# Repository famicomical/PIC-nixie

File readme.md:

# PIC-nixie #
Design of a simple yet accurate Nixie clock controlled by a single-chip MCU. 

Logic Board:

Socket Board for IN-14 Tubes:

The socket PCB plugs into the logic board to make an 'L' shape.

The time is displayed on four tubes with MUX-ed cathodes. The digits are output in binary-coded decimal for interfacing with the K155ID1 cathode driver. Anodes and the colon bulb (12:34) are also controlled by the PIC through BJT-pMOS level shifters.

The program tracks time such that the bottle-neck for clock accuracy will be the external oscillator. Anode blanking was implemented to ensure fast transitions on the Nixie tubes without ghosting (with help from a Zener diode). The clock will also run an outgassing routine every hour to prevent "cathode poisoning" and even out wear to lengthen tube life.

A CR2032 battery can be installed on the circuit board to provide backup power in the event of an outage. The tubes may go dark but the MCU will continue to run and keep time for about 11 hours until power is restored.

## Design

The PCB assembly is housed in a 'C'-shaped enclosure, which obscures the tops of the neon tubes. The design was developed in collaboration with my friend [Donald Swen](https://www.dswenn.com/projects/2019/11/27/22-Design.html) at Stanford's Design School. The idea is that, by hiding the pointed tops of the IN-14 tubes, the finished clock can achieve a symettry that would normally only be possible with IN-12 bulbs. With this clock shape, the vertical digits appear to be floating seamlessly within a cylinder. PIC-Nixie is the first neon tube clock to incorporate this aesthetic design principle.

The enclosure for the prototype was made from stacked slabs of Fraké wood. The clock was a gift for my grandpa.

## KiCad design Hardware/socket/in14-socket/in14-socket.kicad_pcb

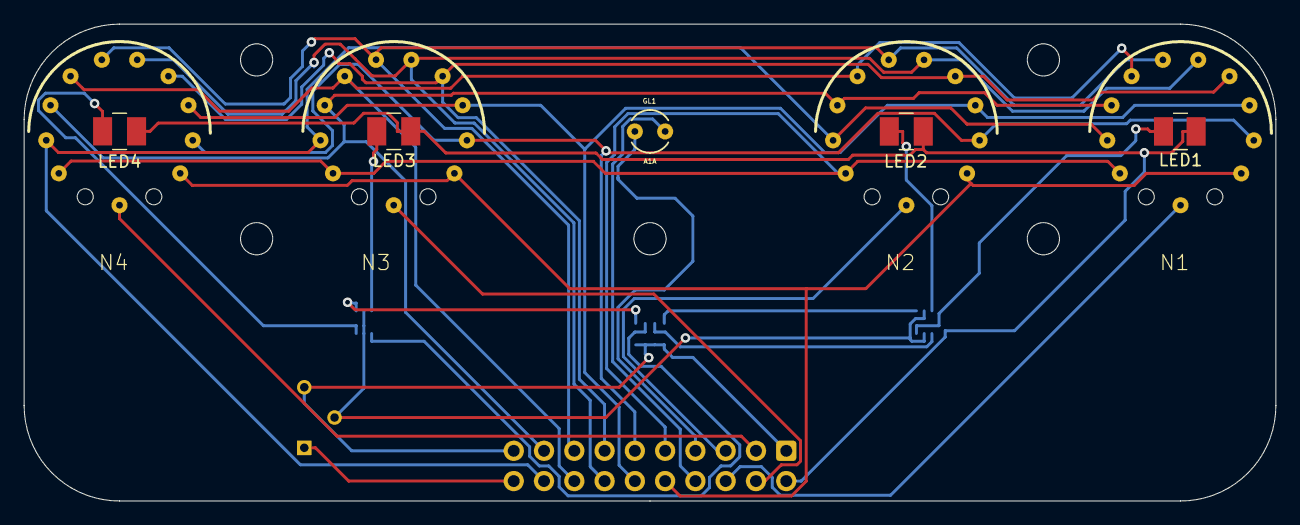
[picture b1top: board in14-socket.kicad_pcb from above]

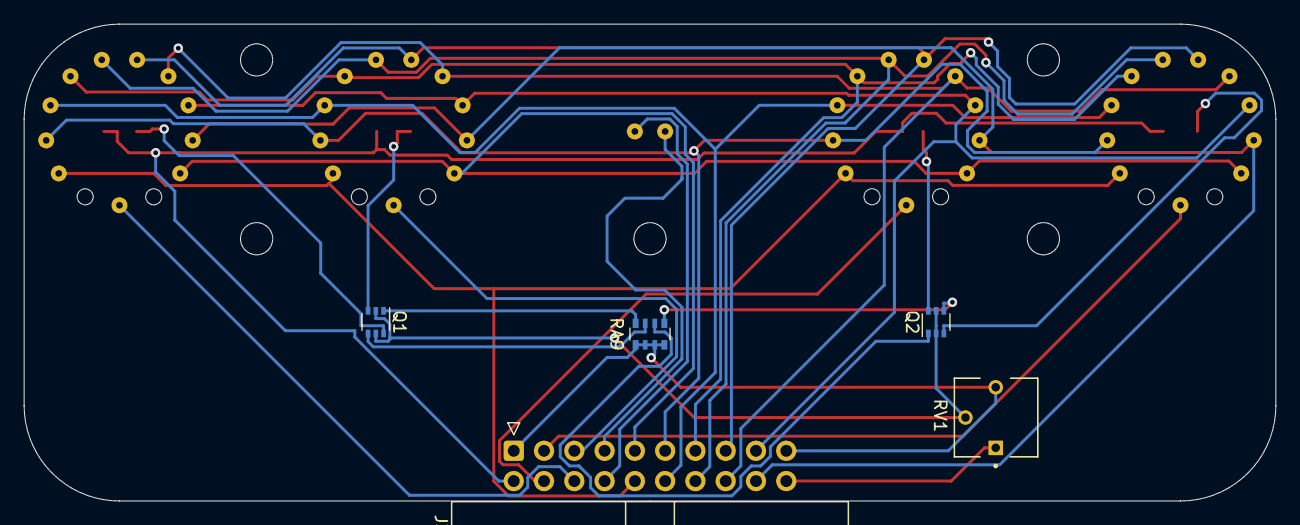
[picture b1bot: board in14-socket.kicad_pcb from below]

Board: 2 copper layers, 105.0 x 40.0 mm, 19 parts (5 on the bottom side), 28 nets.

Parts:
GL1: A1A; NE2-A1A
H1, H2, H3, H4, H5: MountingHole_2.7mm_M2.5
J3: Conn_01x20_Male; IDC-Header_2x10_P2.54mm_Horizontal
LED1, LED2, LED3, LED4: VLMU3100-GS08
N1, N2, N3, N4: Val**; IN-14
Q1, Q2: BC847BS; SOT-363_SC-70-6
RA9: 220 x 4; R_Array_Convex_4x0603
RV1: R_POT_TRIM_US; TRIM_3362P-1-302LF

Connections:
+3V0: J3.20, RV1.1
/HR1: J3.5, N2.A
/HR10: J3.6, N1.A
/MIN1: J3.3, N4.A
/MIN10: J3.4, N3.A
/colon1: GL1.1, J3.7
/colon2: GL1.2, J3.8
GND: J3.1, J3.19, RA9.1, RA9.2, RA9.3, RA9.4, RV1.3
unnamed: J3.9, N1.0, N2.0, N3.0, N4.0
unnamed: J3.10, N1.1, N2.1, N3.1, N4.1
unnamed: J3.11, N1.2, N2.2, N3.2, N4.2
unnamed: J3.12, N1.3, N2.3, N3.3, N4.3
unnamed: J3.13, N1.4, N2.4, N3.4, N4.4
unnamed: J3.14, N1.5, N2.5, N3.5, N4.5
unnamed: J3.15, N1.6, N2.6, N3.6, N4.6
unnamed: J3.16, N1.7, N2.7, N3.7, N4.7
unnamed: J3.17, N1.8, N2.8, N3.8, N4.8
unnamed: J3.18, N1.9, N2.9, N3.9, N4.9
unnamed: LED1.1, Q1.6
unnamed: LED2.1, Q1.3
unnamed: LED3.1, Q2.6
unnamed: LED4.1, Q2.3
unnamed: Q1.1, RA9.8
unnamed: Q1.2, Q1.5, Q2.2, Q2.5, RV1.2
unnamed: Q1.4, RA9.7
unnamed: Q2.1, RA9.6
unnamed: Q2.4, RA9.5
VCC: J3.2, LED1.2, LED2.2, LED3.2, LED4.2

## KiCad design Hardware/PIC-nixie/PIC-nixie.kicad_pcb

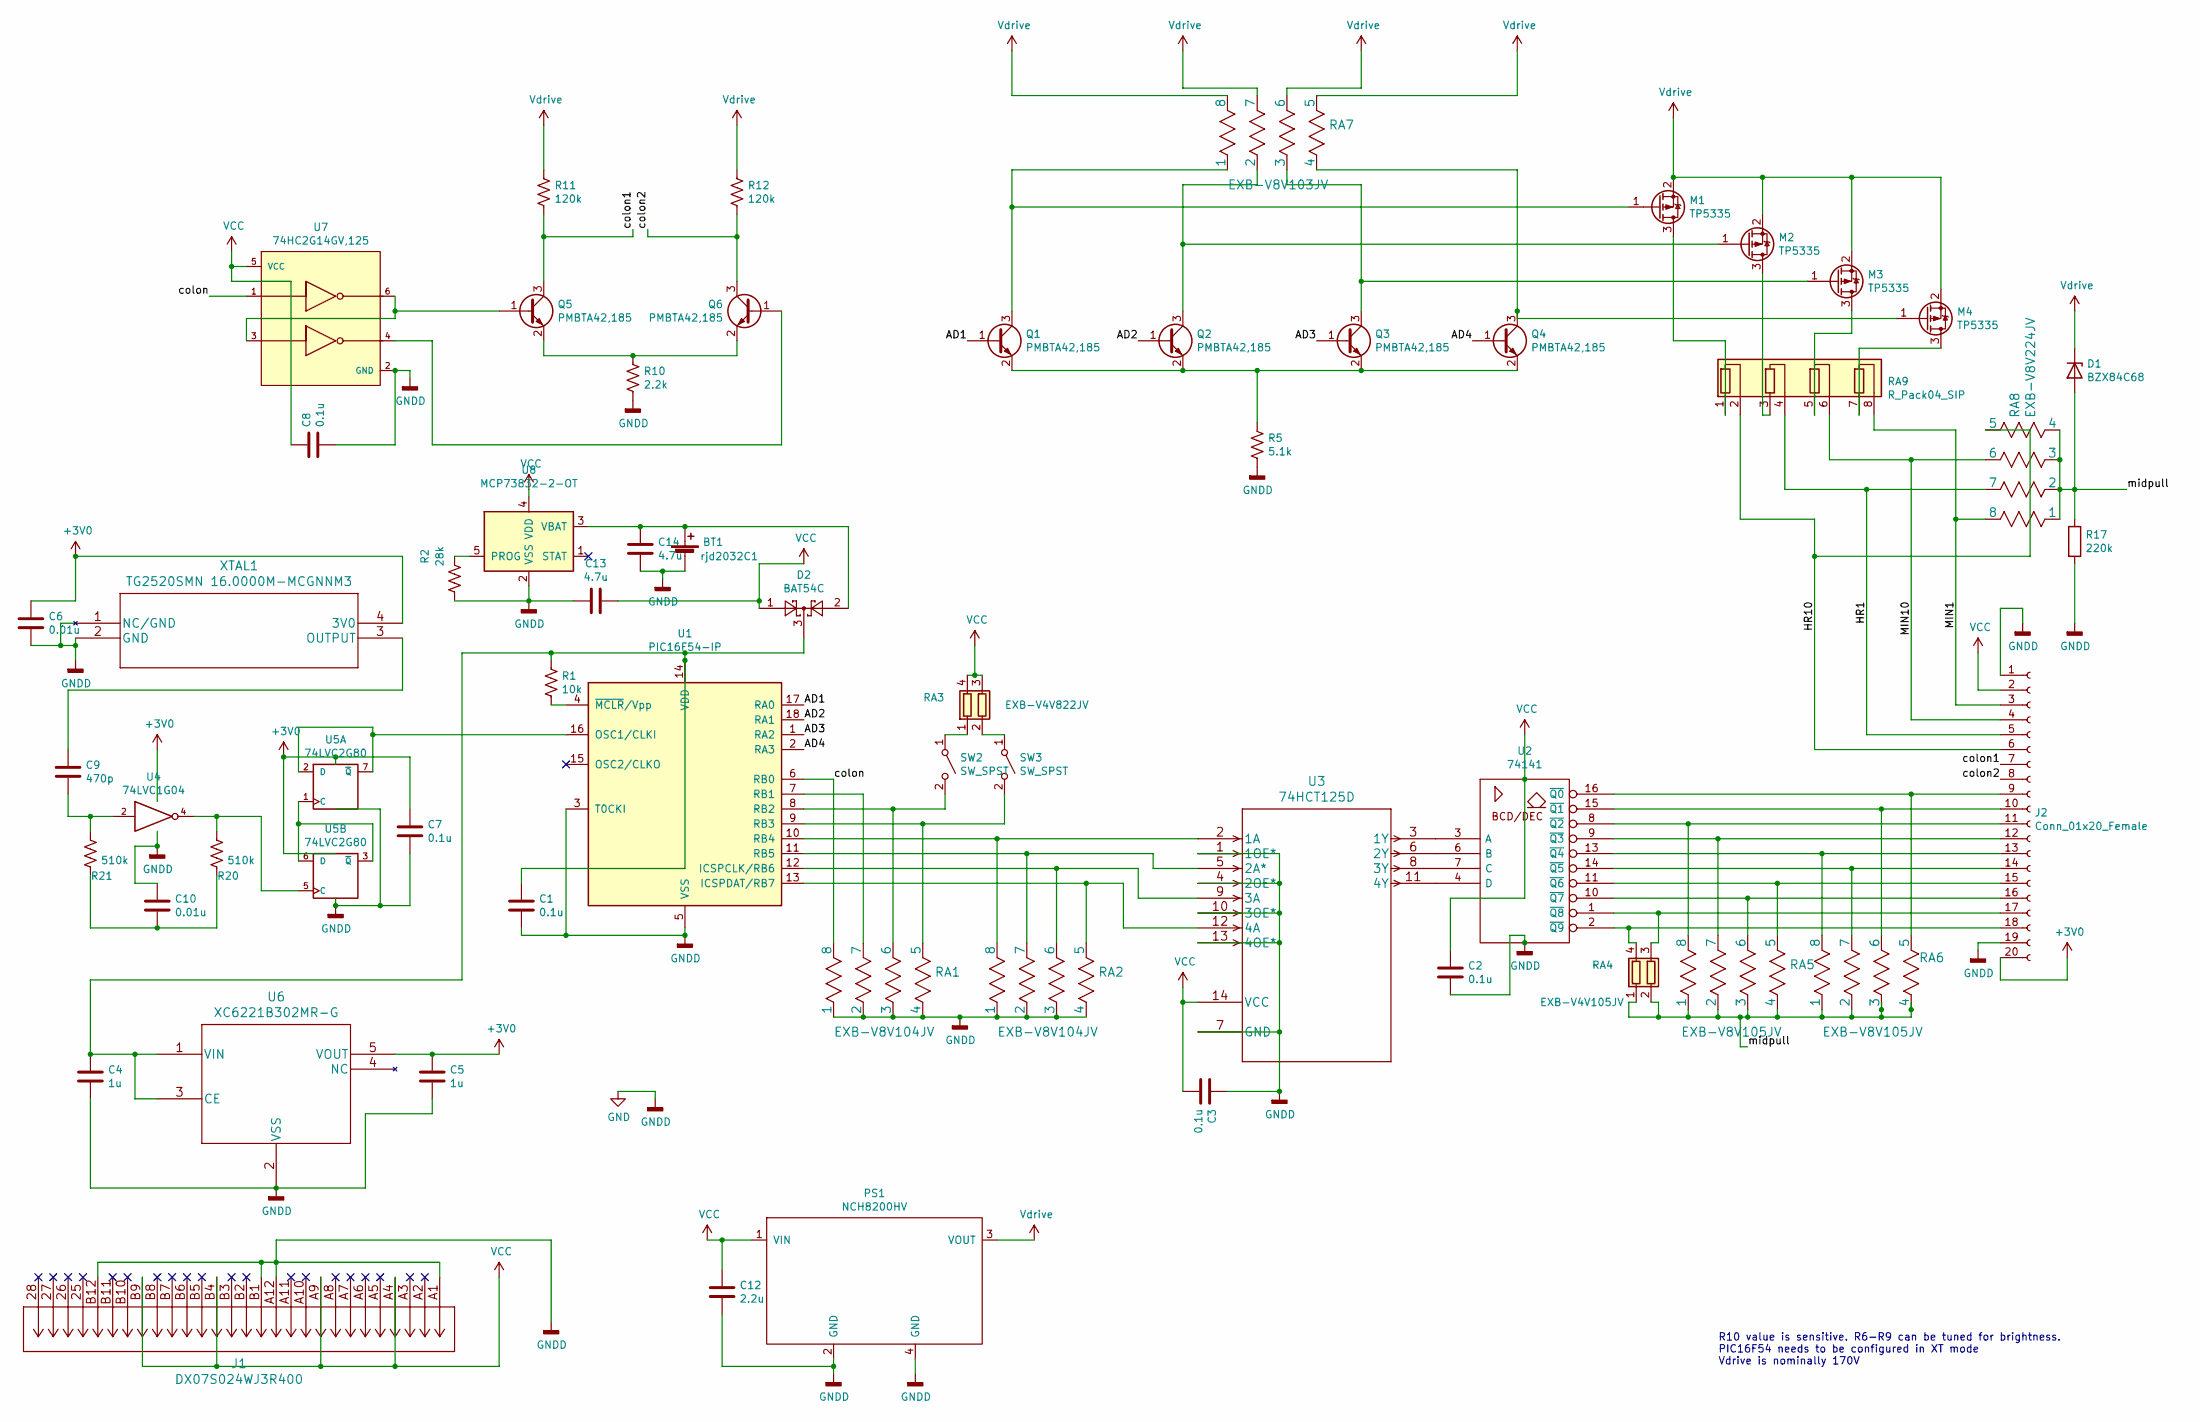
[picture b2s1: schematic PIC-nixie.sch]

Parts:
BT1: rjd2032C1; BatteryHolder_Keystone_1060_1x2032
C1, C2, C3, C7, C8: 0.1u; C_0603_1608Metric_Pad1.05x0.95mm_HandSolder
C4, C5: 1u; C_0603_1608Metric_Pad1.05x0.95mm_HandSolder
C6, C10: 0.01u; C_0603_1608Metric_Pad1.05x0.95mm_HandSolder
C9: 470p; C_0603_1608Metric_Pad1.05x0.95mm_HandSolder
C12: 2.2u; C_0805_2012Metric_Pad1.15x1.40mm_HandSolder
C13, C14: 4.7u; C_0805_2012Metric_Pad1.15x1.40mm_HandSolder
D1: BZX84C68; D_SOT-23_ANK
D2: BAT54C; SOT-23
J1: DX07S024WJ3R400; JAE_DX07S024WJ3R400
J2: Conn_01x20_Female; IDC-Header_2x10_P2.54mm_Vertical
M1, M2, M3, M4: TP5335; SOT-23
PS1: NCH8200HV
Q1, Q2, Q3, Q4, Q5, Q6: PMBTA42,185; SOT-23
R1: 10k; R_0805_2012Metric_Pad1.15x1.40mm_HandSolder
R2: 28k; R_0805_2012Metric_Pad1.15x1.40mm_HandSolder
R5: 5.1k; R_0805_2012Metric_Pad1.15x1.40mm_HandSolder
R10: 2.2k; R_0805_2012Metric_Pad1.15x1.40mm_HandSolder
R11, R12: 120k; R_0805_2012Metric_Pad1.15x1.40mm_HandSolder
R17: 220k; R_0805_2012Metric_Pad1.15x1.40mm_HandSolder
R20, R21: 510k; R_0603_1608Metric_Pad0.98x0.95mm_HandSolder
RA1, RA2: EXB-V8V104JV; R_Array_Convex_4x0603
RA3: EXB-V4V822JV; R_Array_Convex_2x0603
RA4: EXB-V4V105JV; R_Array_Convex_2x0603
RA5, RA6: EXB-V8V105JV; R_Array_Convex_4x0603
RA7: EXB-V8V103JV; R_Array_Convex_4x0603
RA8: EXB-V8V224JV; R_Array_Convex_4x0603
RA9: R_Pack04_SIP; R_Array_SIP8
SW2, SW3: SW_SPST; SW_TL3301SPF260QG
U1: PIC16F54-IP; DIP-18_W7.62mm_Socket
U2: 74141; DIP-16_W7.62mm_Socket
U3: 74HCT125D; SOIC-14_3.9x8.7mm_P1.27mm
U4: 74LVC1G04; SOT-553
U5: 74LVC2G80; VSSOP-8_2.3x2mm_P0.5mm
U6: XC6221B302MR-G
U7: 74HC2G14GV,125; Nexperia-SOT457-11_2018-0-MFG; mouser part number 771-HC2G14GV125; digikey description IC INVERTER SCHMITT 2CH 6TSOP
U8: MCP73832-2-OT; SOT-23-5
XTAL1: TG2520SMN 16.0000M-MCGNNM3

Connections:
+3V0: C5.1, C6.1, C7.1, J2.20, U4.5 (+V), U5.8 (+V), U6.5 (VOUT), XTAL1.4 (3V0); also elsewhere on the board
/AD1: Q1.1 (B), U1.17 (RA0)
/AD2: Q2.1 (B), U1.18 (RA1)
/AD3: Q3.1 (B), U1.1 (RA2)
/AD4: Q4.1 (B), U1.2 (RA3)
/HR1: J2.5, RA8.7, RA9.4 (R2.2)
/HR10: J2.6, RA8.5, RA9.2 (R1.2)
/MIN1: J2.3, RA8.8, RA9.8 (R4.2)
/MIN10: J2.4, RA8.6, RA9.6 (R3.2)
/colon: RA1.8, U1.6 (RB0), U7.1 (1A)
/colon1: J2.7, Q5.3 (C), R11.2
/colon2: J2.8, Q6.3 (C), R12.2
/midpull: D1.2 (A), R17.1, RA4.1 (R1.1), RA4.2 (R2.1), RA5.1, RA5.2, RA5.3, RA5.4, RA6.1, RA6.2, RA6.3, RA6.4, RA8.1, RA8.2, RA8.3, RA8.4
GND: BT1.2 (-), C1.2, C2.2, C3.1, C4.2, C5.2, C6.2, C7.2, C8.2, C10.1, C12.2, C13.2, C14.2, J1.A1, J1.A12, J1.B1, J1.B12, J2.1, J2.19, PS1.2 (GND), PS1.4 (GND), R2.2, R5.2, R10.2, R17.2, RA1.1, RA1.2, RA1.3, RA1.4, RA2.1, RA2.2, RA2.3, RA2.4, U1.3 (T0CKI), U1.5 (VSS), U2.12 (GND), U3.1 (1OE*), U3.4 (2OE*), U3.7 (GND), U3.10 (3OE*), U3.13 (4OE*), U4.3 (GND), U5.4 (GND), U6.2 (VSS), U7.2 (GND), U8.2 (VSS), XTAL1.1 (NC/GND), XTAL1.2 (GND); also elsewhere on the board
unnamed: BT1.1 (+), C14.1, D2.2, U8.3 (VBAT)
unnamed: C1.1, C4.1, D2.3, R1.1, U1.14 (VDD), U6.1 (VIN), U6.3 (CE)
unnamed 16: C9.1, XTAL1.3 (OUTPUT); also elsewhere on the board
unnamed: C9.2, R21.1, U4.2
unnamed: C10.2, R20.2, R21.2
unnamed: J2.9, RA6.5, U2.16 (~Q0)
unnamed: J2.10, RA6.6, U2.15 (~Q1)
unnamed: J2.11, RA5.8, U2.8 (~Q2)
unnamed: J2.12, RA5.7, U2.9 (~Q3)
unnamed: J2.13, RA6.8, U2.13 (~Q4)
unnamed: J2.14, RA6.7, U2.14 (~Q5)
unnamed: J2.15, RA5.5, U2.11 (~Q6)
unnamed: J2.16, RA5.6, U2.10 (~Q7)
unnamed: J2.17, RA4.3 (R2.2), U2.1 (~Q8)
unnamed: J2.18, RA4.4 (R1.2), U2.2 (~Q9)
unnamed: M1.1 (G), Q1.3 (C), RA7.1
unnamed: M1.3 (D), RA9.1 (R1.1)
unnamed: M2.1 (G), Q2.3 (C), RA7.2
unnamed: M2.3 (D), RA9.3 (R2.1)
unnamed: M3.1 (G), Q3.3 (C), RA7.3
unnamed: M3.3 (D), RA9.5 (R3.1)
unnamed: M4.1 (G), Q4.3 (C), RA7.4
unnamed: M4.3 (D), RA9.7 (R4.1)
unnamed: Q1.2 (E), Q2.2 (E), Q3.2 (E), Q4.2 (E), R5.1
unnamed: Q5.1 (B), U7.3 (2A), U7.6 (1Y)
unnamed: Q5.2 (E), Q6.2 (E), R10.1
unnamed: Q6.1 (B), U7.4 (2Y)
unnamed: R1.2, U1.4 (~MCLR~/Vpp)
unnamed: R2.1, U8.5 (PROG)
unnamed: R20.1, U4.4, U5.5 (C)
unnamed: RA1.5, SW3.2 (B), U1.9 (RB3)
unnamed: RA1.6, SW2.2 (B), U1.8 (RB2)
unnamed: RA1.7, U1.7 (RB1)
unnamed: RA2.5, U1.13 (ICSPDAT/RB7), U3.12 (4A)
unnamed: RA2.6, U1.12 (ICSPCLK/RB6), U3.9 (3A)
unnamed: RA2.7, U1.11 (RB5), U3.5 (2A*)
unnamed: RA2.8, U1.10 (RB4), U3.2 (1A)
unnamed: RA3.1 (R1.1), SW2.1 (A)
unnamed: RA3.2 (R2.1), SW3.1 (A)
unnamed: U1.16 (OSC1/CLKI), U5.2 (D), U5.7 (~Q)
unnamed: U2.3 (A), U3.3 (1Y)
unnamed: U2.4 (D), U3.11 (4Y)
unnamed: U2.6 (B), U3.6 (2Y)
unnamed: U2.7 (C), U3.8 (3Y)
unnamed: U5.1 (C), U5.3 (~Q), U5.6 (D)
VCC: C2.1, C3.2, C8.1, C12.1, C13.1, D2.1, J1.A4, J1.A9, J1.B4, J1.B9, J2.2, PS1.1 (VIN), RA3.3 (R2.2), RA3.4 (R1.2), U2.5 (VCC), U3.14 (VCC), U7.5 (VCC), U8.4 (VDD)
Vdrive: D1.1 (K), M1.2 (S), M2.2 (S), M3.2 (S), M4.2 (S), PS1.3 (VOUT), R11.1, R12.1, RA7.5, RA7.6, RA7.7, RA7.8

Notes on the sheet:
R10 value is sensitive. R6-R9 can be tuned for brightness. PIC16F54 needs to be configured in XT mode Vdrive is nominally 170V

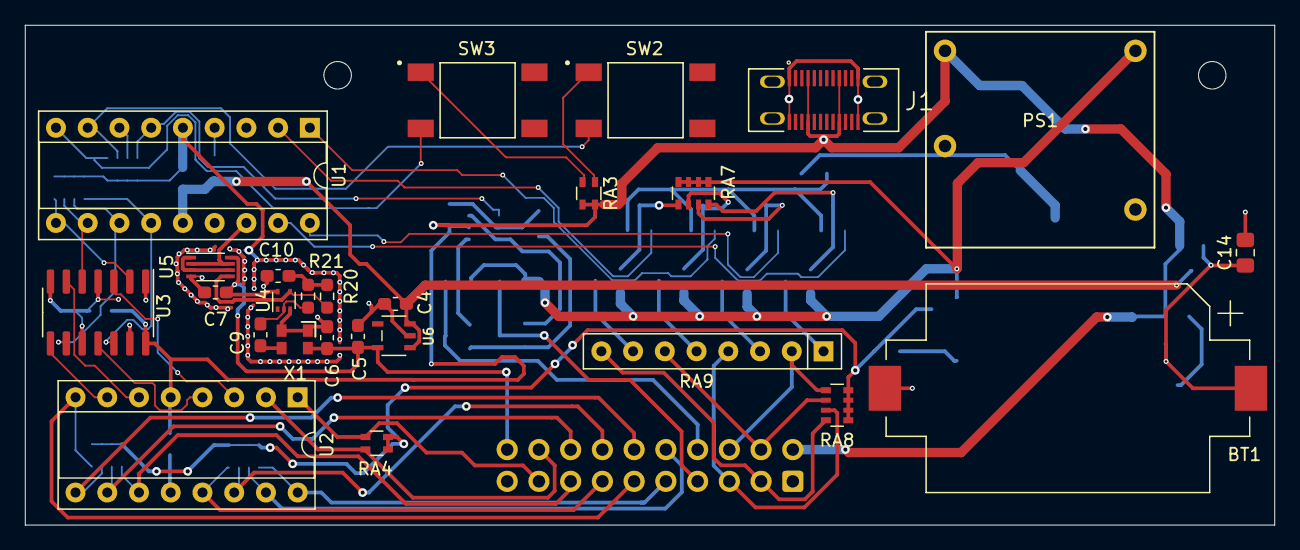
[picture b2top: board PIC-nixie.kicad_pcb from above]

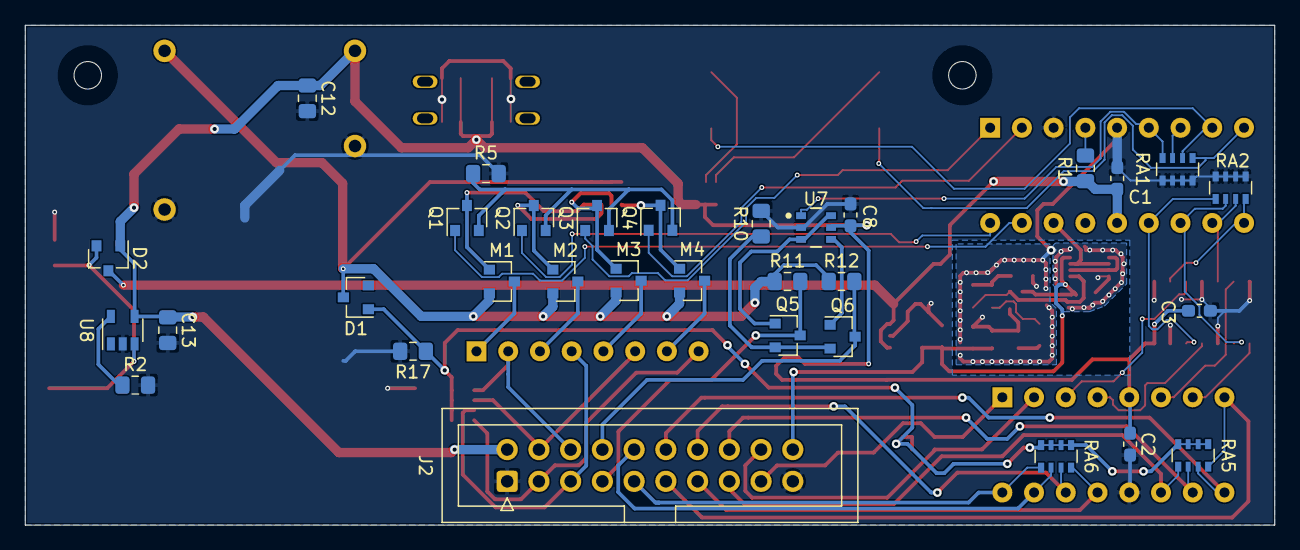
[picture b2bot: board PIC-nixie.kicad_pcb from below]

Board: 2 copper layers, 100.0 x 40.0 mm, 58 parts (32 on the bottom side), 61 nets.

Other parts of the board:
X1: TG2520SMN 16.0000M-MCGNNM3

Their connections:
+3V0: X1.4; also elsewhere on the board
GND: X1.1, X1.2; also elsewhere on the board
unnamed 16: X1.3; also elsewhere on the board

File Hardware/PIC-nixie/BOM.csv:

Item,Reference(s),Value,Footprint,digikey part number,Qty,
1,"C1, C2, C3, C7, C8",0.1u,SM0603,1276-1941-2-ND,5,
2,"C4, C5",1u,SM0603,445-12539-2-ND ,2,
3,"C6, C10",0.01u NP0,SM0603,478-3700-2-ND,2,
4,C9,470p NP0,SM0603,478-5777-2-ND ,1,
5,C11,2.2u film,external:QXK2E225KTP,493-3523-ND,1,
6,C12,2.2u,SM0805,1276-2953-2-ND,1,
7,D1,BZX84C68,SOT-23,BZX84C68LT1GOSTR-ND,1,
8,J1,DX07S024WJ3R400,external:DX07S024WJ3R400,670-2950-2-ND ,1,
9,J2,Conn_01x20_Female,Connector_IDC:IDC-Header_2x10_P2.54mm_Vertical,S9197-ND ,1,
10,"M1, M2, M3, M4",TP5335,SOT-23,TP5335K1-GTR-ND,4,
11,PS1,NCH8200HV,PIC-nixie:NCH8200HV,N/A,1,
12,"Q1, Q2, Q3, Q4, Q5, Q6","PMBTA42,185",SOT-23,1727-8537-2-ND,6,
13,R1,10k,Resistor_SMD:R_0805_2012Metric_Pad1.15x1.40mm_HandSolder,2019-SG73S2ATTD103JTR-ND,1,
14,R5,5.1k,Resistor_SMD:R_0805_2012Metric_Pad1.15x1.40mm_HandSolder,P21099TR-ND,1,
15,R10,2.2k,Resistor_SMD:R_0805_2012Metric_Pad1.15x1.40mm_HandSolder,2019-SG73S2ATTD2201FTR-ND,1,
16,"R11, R12",120k,Resistor_SMD:R_0805_2012Metric_Pad1.15x1.40mm_HandSolder,2019-RK73H2ARTTD1203FTR-ND,2,
17,R17,220k,Resistor_SMD:R_0805_2012Metric_Pad1.15x1.40mm_HandSolder,A126350TR-ND ,1,
18,"R20, R21",510k,Resistor_SMD:R_0603_1608Metric_Pad0.98x0.95mm_HandSolder,YAG4802TR-ND,2,
19,"RA1, RA2, RA7",EXB-V8V103JV,Resistor_SMD:R_Array_Convex_4x0603,Y4103TR-ND,3,
20,RA3,EXB-V8V821JV,Resistor_SMD:R_Array_Convex_4x0603,Y4821TR-ND ,1,
21,RA4,EXB-V4V105JV,Resistor_SMD:R_Array_Convex_2x0603,Y2105TR-ND,1,
22,"RA5, RA6",EXB-V8V105JV,Resistor_SMD:R_Array_Convex_4x0603,Y4105TR-ND,2,
23,RA8,EXB-V8V224JV,Resistor_SMD:R_Array_Convex_4x0603,Y4224TR-ND,1,
24,RA9,4608X-102-822LF,Resistor_THT:R_Array_SIP8,4608X-2-822LF-ND ,1,
25,"SW1, SW2, SW3",SW_SPST,external:SW_TL3301SPF260QG,EG1870TR-ND,3,
26,U1,PIC16F54-IP,Package_DIP:DIP-18_W7.62mm_Socket,"PIC16F54-I/P-ND, ED3318-ND",1,
27,U2,K155ID1,Package_DIP:DIP-16_W7.62mm_Socket,"N/A, ED90033-ND",1,
28,U3,74HCT125D,external:74HCT125D,1727-2834-2-ND ,1,
29,U4,74LVC1G04,Package_TO_SOT_SMD:SOT-553,74LVC1G04Z-7DITR-ND ,1,
30,U5,74LVC2G80,Package_SO:VSSOP-8_2.3x2mm_P0.5mm,296-17083-2-ND,1,
31,U6,XC6221B302MR-G,external:XC6221B302MR-G,893-1100-2-ND,1,
32,U7,"74HC2G14GV,125",ext2:Nexperia-SOT457-11_2018-0-MFG,1727-6046-1-ND,1,
33,XTAL1,"I537-2O7-16.000, TG2520SMN 16",PIC-nixie:Crystal_SMD_ILSI_I537-4Pin_3.2x2.5mm,2780-I537-2O7-16.000MHZTR-ND,1, 732-TG252S16MCGNNM3

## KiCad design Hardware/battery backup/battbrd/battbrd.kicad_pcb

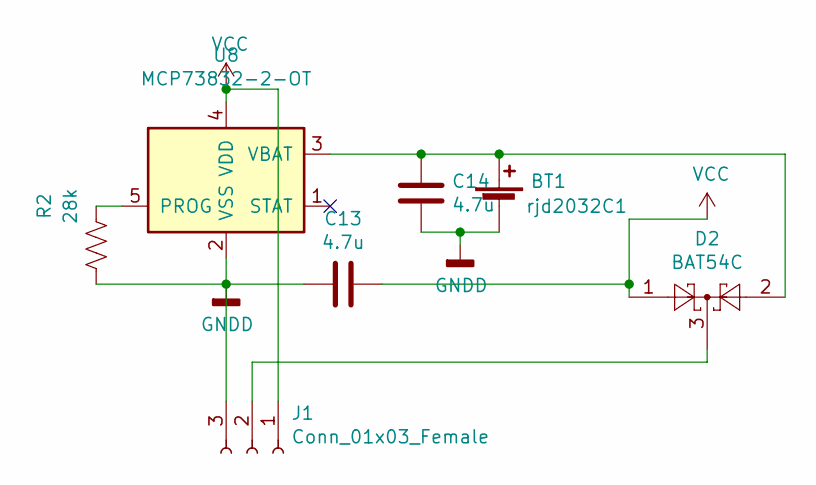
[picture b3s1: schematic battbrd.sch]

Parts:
BT1: rjd2032C1; BatteryHolder_Keystone_1060_1x2032
C13, C14: 4.7u; C_0805_2012Metric_Pad1.15x1.40mm_HandSolder
D2: BAT54C; SOT-23
J1: Conn_01x03_Female; PinHeader_1x03_P2.00mm_Vertical_SMD_Pin1Left
R2: 28k; R_0805_2012Metric_Pad1.15x1.40mm_HandSolder
U8: MCP73832-2-OT; SOT-23-5

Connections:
GNDD: BT1.2 (-), C13.2, C14.2, J1.3, R2.2, U8.2 (VSS)
unnamed: BT1.1 (+), C14.1, D2.2, U8.3 (VBAT)
unnamed: D2.3, J1.2
unnamed: R2.1, U8.5 (PROG)
VCC: C13.1, D2.1, J1.1, U8.4 (VDD)

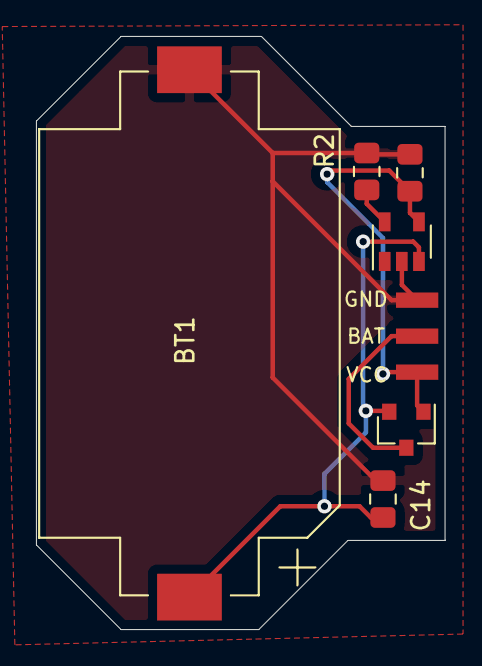
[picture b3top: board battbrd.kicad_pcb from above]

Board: 2 copper layers, 22.7 x 32.9 mm, 7 parts (0 on the bottom side), 5 nets.

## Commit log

2021-03-12 firstcommit
2021-03-12 add readme
2021-03-28 add docs
2021-03-28 in-14 datasheets
2021-03-28 reduce filesize
2021-04-12 add docs, comment and format code
2021-04-14 fully adapted pic code. assembles, but not debugged
2021-04-15 add cathode poisoning prevention routine
2021-04-15 ignore some files
2021-11-09 changed TCXO, PCB layout completed
2021-11-12 logic PCB tweaks, resize
2021-11-16 PCB as submitted to fab
2021-11-22 fix switch pin assignment, reduce hole size on nixie sockets
2022-08-04 add battery backup for power failures
2023-03-17 update 3D view, add figures
2023-03-17 relocate libraries for socket boards, fix routing & 3D models
2023-03-17 fix routing on in-14 socket, make figures
2023-04-04 update figures
2023-04-04 add photo
2023-04-04 update schema

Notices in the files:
parts and their libraries:
Copyright 2021 Accelerated Designs. All rights reserved.
